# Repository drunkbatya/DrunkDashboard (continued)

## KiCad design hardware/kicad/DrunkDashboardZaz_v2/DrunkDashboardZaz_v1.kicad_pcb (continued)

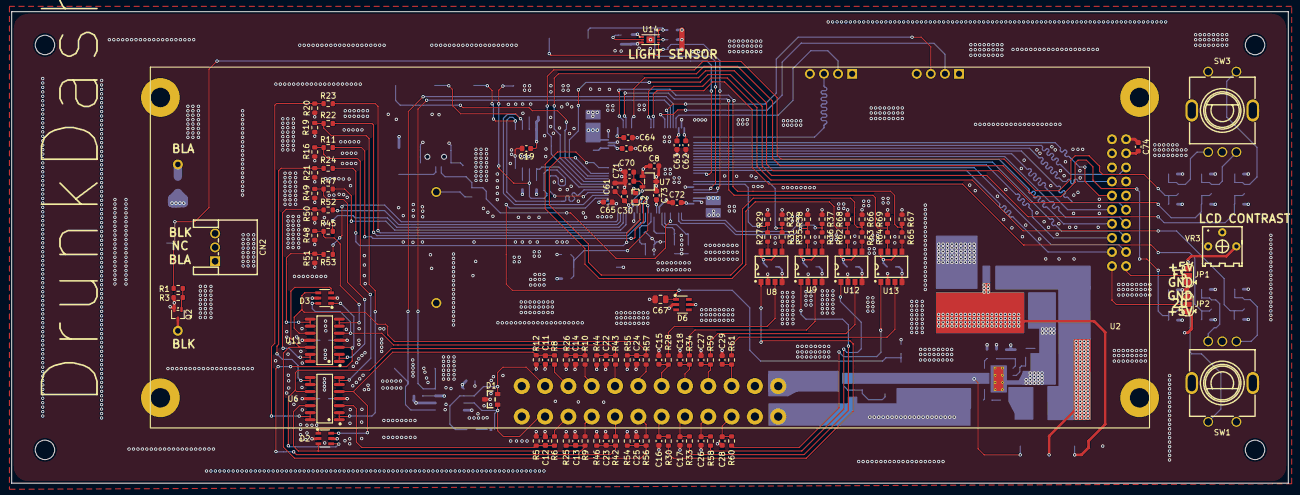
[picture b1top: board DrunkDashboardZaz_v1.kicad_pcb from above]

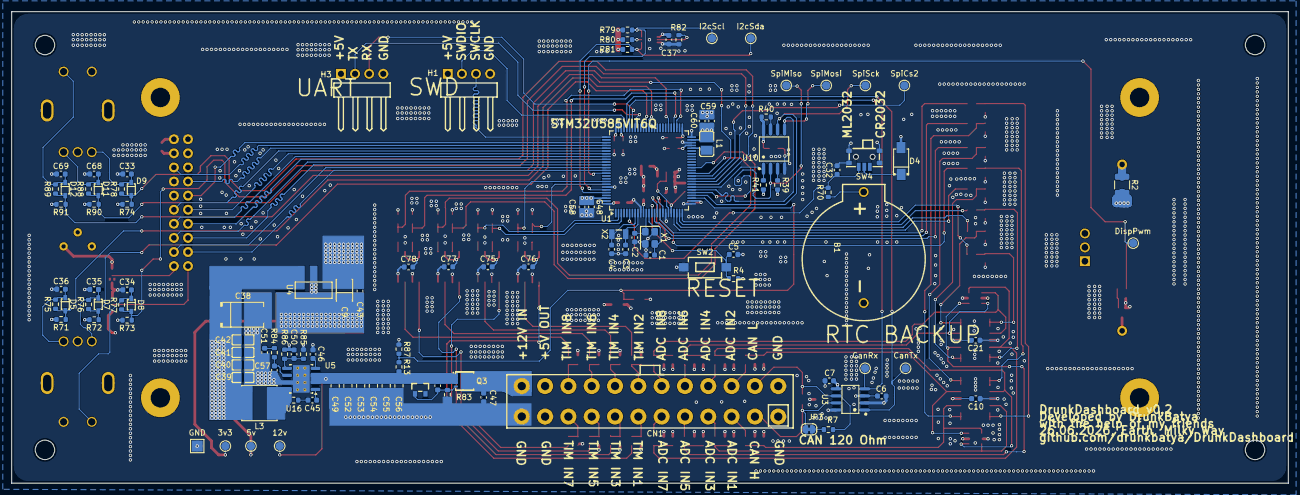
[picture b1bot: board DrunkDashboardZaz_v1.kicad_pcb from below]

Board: 4 copper layers, 230.0 x 84.9 mm, 223 parts (113 on the bottom side), 141 nets.

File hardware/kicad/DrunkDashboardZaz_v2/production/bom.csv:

Designator,Footprint,Quantity,Value,LCSC Part #
12V_1,TestPoint_Pad_D1.5mm,1,12v,
3V3_1,TestPoint_Pad_D1.5mm,1,3v3,
5V1,TestPoint_Pad_D1.5mm,1,5v,
B1,BS-02-A1AJ010,1,BS-02-A1AJ010,C5239862
"C1, C2, C3, C4",0603,4,CL10C180JB8NNNC,C1647
"C10, C11, C12, C13, C14, C15, C16, C17, C18, C19, C21, C22, C23, C24, C25, C26, C27, C28, C29, C30, C32, C37, C44, C45, C46, C48, C59, C6, C62, C63, C64, C65, C66, C7, C71, C72, C73, C74, C75, C76, C77, C78, C8",0603,43,CL10B104KB8NNNC,C1591
"C33, C34, C35, C36, C5, C68, C69",0603,7,CC0603KRX7R0BB103,C107059
C38,EEFCX0J101R,1,EEFCX0J101R,C189619
"C39, C40, C41, C42",GCM21BR71A106KE22L,4,GCM21BR71A106KE22L,C126586
C43,0603,1,CL10A475KO8NNNC,C19666
C47,0603,1,CC0603KRX7R0BB104,C113803
"C49, C52, C53, C54, C55, C56, C67",0805,7,GRM21BC8YA106KE11L,C469541
"C50, C57",0603,2,CC0603KRX7R0BB221,C107061
C51,0603,1,CC0603KRX7R9BB122,C107073
"C58, C60, C61",0603,3,GRM188R61H225KE11D,C162273
C70,0603,1,CC0603JRX7R7BB105,C519560
C9,25TQC22MYFB,1,25TQC22MYFB,C3018703
CANRX_1,TestPoint_Pad_D1.5mm,1,CanRx,
CANTX_1,TestPoint_Pad_D1.5mm,1,CanTx,
CN1,39281243,1,39281243,C114088
CN2,S3B-XH-A-1_LF_SN,1,S3B-XH-A-1_LF_SN,C163036
D1,PESD1CAN_215,1,PESD1CAN_215,C15771
D10,MMBZ5242BLT3G,1,MMBZ5242BLT3G,C896784
"D11, D12, D5, D7, D8, D9",1N4148WS_C917117,6,1N4148WS_C917117,C917117
"D2, D3, D6",SRV05-4_C558418,3,SRV05-4_C558418,C558418
D4,SS12_C18199177,1,SS12_C18199177,C18199177
DISPPWM1,TestPoint_Pad_D1.5mm,1,DispPwm,
GND1,TestPoint_Pad_2.0x2.0mm,1,GND,
"H1, H3",PZ254R-11-04P,2,PZ254R-11-04P,C492412
I2CSCL_1,TestPoint_Pad_D1.5mm,1,I2cScl,
I2CSDA_1,TestPoint_Pad_D1.5mm,1,I2cSda,
L1,LQM2HPN2R2MG0L,1,LQM2HPN2R2MG0L,C86092
L2,BLM18PG121SN1D_C14709,1,BLM18PG121SN1D_C14709,C14709
L3,SRN6045TA-3R3Y,1,SRN6045TA-3R3Y,C3221229
Q2,SOT-323_SC-70,1,2N7002WT1G,C232391
Q3,DMP3013SFV-7_ES,1,DMP3013SFV-7_ES,C42412325
"R1, R70",0603,2,PTFR0603B100RN9,C394538
"R10, R16, R19, R20, R21, R3, R39, R4, R40, R41, R42, R43, R48, R49, R50, R51, R56, R57, R6, R71, R72, R73, R74, R75, R76, R77, R78, R8, R87, R88, R89, R9, R90, R91",0603,34,RT0603BRD0710KL,C95204
"R11, R22, R23, R24, R45, R47, R52, R53",0603,8,FRC0603F5601TS,C2907046
R13,0603,1,FRC0603F8202TS,C2907072
R2,1210,1,RK73B2ETTD180J,C830159
"R27, R31, R35, R36, R62, R63, R64, R65",0603,8,FRC0603F2401TS,C2907007
"R28, R30, R33, R34, R58, R59, R60, R61",0603,8,FRC0603F6200TS,C2907058
"R29, R32, R37, R38, R66, R67, R68, R69, R79, R81, R82",0603,11,FRC0603F4701TS,C2907034
"R44, R46, R54, R55",0603,4,FRC0603F2701TS,C2907008
R7,0603,1,FRC0603F1200TS,C2906988
R80,0603,1,FRC0603F1001TS,C2907002
"R83, R86",0603,2,RC0603FR-0712KL,C114659
R84,0603,1,FRC0603F2002TS,C2907011
R85,0603,1,FRC0603F2201TS,C2907005
SPICS2_1,TestPoint_Pad_D1.5mm,1,SpiCs2,
SPIMISO_1,TestPoint_Pad_D1.5mm,1,SpiMiso,
SPIMOSI_1,TestPoint_Pad_D1.5mm,1,SpiMosi,
SPISCK_1,TestPoint_Pad_D1.5mm,1,SpiSck,
"SW1, SW3",EC11E15244G1,2,EC11E15244G1,C370970
SW2,TS3643TP,1,TS3643TP,C398054
SW4,MINI_MSK12CO2,1,MINI_MSK12CO2,C2681570
U1,LQFP-100_14x14mm_P0.5mm,1,STM32U585VIT6Q,C5270986
U10,W25Q32JVSSIQ_C179173,1,W25Q32JVSSIQ_C179173,C179173
"U11, U6",MCP6004T-I_SL,2,MCP6004T-I_SL,C7378
"U12, U13, U8, U9",ILD207T,4,ILD207T,C71049
U14,BH1750FVI-TR,1,BH1750FVI-TR,C78960
U16,0603,1,CRCW060310R0FKEAHP,C313648
U3,TJA1051T_3_1J,1,TJA1051T_3_1J,C38695
U4,AMS1117-3_3,1,AMS1117-3_3,C6186
U5,SOIC-8-1EP_3.9x4.9mm_P1.27mm_EP2.95x4.9mm_Mask2.71x3.4mm_ThermalVias,1,AP64501SP-13,C2071517
U7,REF3333AIDBZR,1,REF3333AIDBZR,C130016
VR3,3362P-1-103LF_C48997950,1,3362P-1-103LF_C48997950,C48997950
X1,Crystal_SMD_3225-4Pin_3.2x2.5mm,1,X322525MOB4SI,C9006
X2,Q13FC1350000400,1,Q13FC1350000400,C32346

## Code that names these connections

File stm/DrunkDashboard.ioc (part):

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Mcu.Name=STM32H743VITx
Mcu.Package=LQFP100
Mcu.UserName=STM32H743VITx
PA12.GPIOParameters=GPIO_Label
PA12.GPIO_Label=BACK_BTN
PA12.Signal=GPIO_Input
PA13\ (JTMS/SWDIO).Mode=Serial_Wire
PA13\ (JTMS/SWDIO).Signal=DEBUG_JTMS-SWDIO
PA14\ (JTCK/SWCLK).Mode=Serial_Wire
PA14\ (JTCK/SWCLK).Signal=DEBUG_JTCK-SWCLK
PA15\ (JTDI).GPIOParameters=GPIO_Label
PA15\ (JTDI).GPIO_Label=NOT_PROVIDED
PA15\ (JTDI).Signal=GPIO_Output
PA2.Mode=Asynchronous
PA2.Signal=USART2_TX
PA3.Mode=Asynchronous
PA3.Signal=USART2_RX
PA5.Mode=TX_Only_Simplex_Unidirect_Master
PA5.Signal=SPI1_SCK
PA6.GPIOParameters=GPIO_Speed,GPIO_Label
PA6.GPIO_Label=SPI1_DC
PA6.GPIO_Speed=GPIO_SPEED_FREQ_LOW
PA6.Signal=GPIO_Output
PA7.Mode=TX_Only_Simplex_Unidirect_Master
PA7.Signal=SPI1_MOSI
PB2.GPIOParameters=GPIO_PuPd,GPIO_Label
PB2.GPIO_Label=DISP4_CS
PB2.GPIO_PuPd=GPIO_PULLUP
PB2.Signal=GPIO_Output
PB4\ (NJTRST).GPIOParameters=GPIO_PuPd,GPIO_Label
PB4\ (NJTRST).GPIO_Label=DISP2_RES
PB4\ (NJTRST).GPIO_PuPd=GPIO_PULLUP
PB4\ (NJTRST).Signal=GPIO_Output
PB5.GPIOParameters=GPIO_PuPd,GPIO_Label
PB5.GPIO_Label=DISP3_RES
PB5.GPIO_PuPd=GPIO_PULLUP
PB5.Signal=GPIO_Output
PB6.GPIOParameters=GPIO_PuPd,GPIO_Label
PB6.GPIO_Label=DISP5_CS
PB6.GPIO_PuPd=GPIO_PULLUP
PB6.Signal=GPIO_Output
PB7.GPIOParameters=GPIO_PuPd,GPIO_Label
PB7.GPIO_Label=DISP3_CS
PB7.GPIO_PuPd=GPIO_PULLUP
PB7.Signal=GPIO_Output
PB8.GPIOParameters=GPIO_PuPd,GPIO_Label
PB8.GPIO_Label=DISP8_CS
PB8.GPIO_PuPd=GPIO_PULLUP
PB8.Signal=GPIO_Output
PB9.GPIOParameters=GPIO_PuPd,GPIO_Label
PB9.GPIO_Label=DISP5_RES
PB9.GPIO_PuPd=GPIO_PULLUP
PB9.Signal=GPIO_Output
PC10.GPIOParameters=GPIO_PuPd,GPIO_Label
PC10.GPIO_Label=DISP9_RES
PC10.GPIO_PuPd=GPIO_PULLUP
PC10.Signal=GPIO_Output
PC11.GPIOParameters=GPIO_PuPd,GPIO_Label
PC11.GPIO_Label=ENC_BTN
PC11.GPIO_PuPd=GPIO_PULLUP
PC11.Signal=GPIO_Input
PC12.GPIOParameters=GPIO_PuPd,GPIO_Label
PC12.GPIO_Label=DISP6_RES
PC12.GPIO_PuPd=GPIO_PULLUP
PC12.Signal=GPIO_Output
PD1.GPIOParameters=GPIO_PuPd,GPIO_Label
PD1.GPIO_Label=DISP9_CS
PD1.GPIO_PuPd=GPIO_PULLUP
PD1.Signal=GPIO_Output
PD4.GPIOParameters=GPIO_PuPd,GPIO_Label
PD4.GPIO_Label=DISP6_CS
PD4.GPIO_PuPd=GPIO_PULLUP
PD4.Signal=GPIO_Output
PD7.GPIOParameters=GPIO_PuPd,GPIO_Label
PD7.GPIO_Label=DISP2_CS
PD7.GPIO_PuPd=GPIO_PULLUP
PD7.Signal=GPIO_Output
PE1.GPIOParameters=GPIO_PuPd,GPIO_Label
PE1.GPIO_Label=DISP8_RES
PE1.GPIO_PuPd=GPIO_PULLUP
PE1.Signal=GPIO_Output
PE10.GPIOParameters=GPIO_PuPd,GPIO_Label
PE10.GPIO_Label=DISP7_RES
PE10.GPIO_PuPd=GPIO_PULLUP
PE10.Signal=GPIO_Output
PE11.Signal=S_TIM1_CH2
PE12.GPIOParameters=GPIO_PuPd,GPIO_Label
PE12.GPIO_Label=DISP1_RES
PE12.GPIO_PuPd=GPIO_PULLUP
PE12.Signal=GPIO_Output
PE13.GPIOParameters=GPIO_PuPd,GPIO_Label
PE13.GPIO_Label=DISP1_CS
PE13.GPIO_PuPd=GPIO_PULLUP
PE13.Signal=GPIO_Output
PE7.GPIOParameters=GPIO_PuPd,GPIO_Label
PE7.GPIO_Label=DISP4_RES
PE7.GPIO_PuPd=GPIO_PULLUP
PE7.Signal=GPIO_Output
PE8.GPIOParameters=GPIO_PuPd,GPIO_Label
PE8.GPIO_Label=DISP7_CS
PE8.GPIO_PuPd=GPIO_PULLUP
PE8.Signal=GPIO_Output
PE9.Signal=S_TIM1_CH1
PH0-OSC_IN\ (PH0).Mode=HSE-External-Oscillator
PH0-OSC_IN\ (PH0).Signal=RCC_OSC_IN
PH1-OSC_OUT\ (PH1).Mode=HSE-External-Oscillator
PH1-OSC_OUT\ (PH1).Signal=RCC_OSC_OUT
RCC.SYSCLKFreq_VALUE=400000000
RCC.SYSCLKSource=RCC_SYSCLKSOURCE_PLLCLK
board=custom

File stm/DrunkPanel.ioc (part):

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Mcu.Name=STM32F411C(C-E)Ux
Mcu.Package=UFQFPN48
Mcu.UserName=STM32F411CEUx
PA4.GPIOParameters=GPIO_Label
PA4.GPIO_Label=SPI1_RST
PA4.Signal=GPIO_Output
PA5.Mode=TX_Only_Simplex_Unidirect_Master
PA5.Signal=SPI1_SCK
PA6.GPIOParameters=GPIO_Label
PA6.GPIO_Label=SPI1_CE
PA6.Signal=GPIO_Output
PA7.Mode=TX_Only_Simplex_Unidirect_Master
PA7.Signal=SPI1_MOSI
PB0.GPIOParameters=GPIO_Label
PB0.GPIO_Label=SPI1_DC
PB0.Signal=GPIO_Output
PB10.Mode=TX_Only_Simplex_Unidirect_Master
PB10.Signal=SPI2_SCK
PB13.GPIOParameters=GPIO_Label
PB13.GPIO_Label=SPI2_DC
PB13.Signal=GPIO_Output
PB14.GPIOParameters=GPIO_Label
PB14.GPIO_Label=SPI2_CE
PB14.Signal=GPIO_Output
PB15.Mode=TX_Only_Simplex_Unidirect_Master
PB15.Signal=SPI2_MOSI
PH0\ -\ OSC_IN.Mode=HSE-External-Oscillator
PH0\ -\ OSC_IN.Signal=RCC_OSC_IN
PH1\ -\ OSC_OUT.Mode=HSE-External-Oscillator
PH1\ -\ OSC_OUT.Signal=RCC_OSC_OUT
RCC.HSE_VALUE=25000000
RCC.SYSCLKFreq_VALUE=100000000
RCC.SYSCLKSource=RCC_SYSCLKSOURCE_PLLCLK
board=custom

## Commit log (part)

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2023-09-12 Init commit
2023-09-12 Remove extra code
2023-09-12 Working single display
2023-09-12 Add working two displays
2023-09-12 Migrating to STM32H7
2023-09-13 Add setiing FIFO threshold
2023-09-13 Trying to use SPI init from example
2023-09-14 SPI works!!
2023-09-14 Format code, add glue
2023-09-15 Starting porting canvas
2023-09-16 Add icons
2023-09-16 Add first icon
2023-09-17 Add mlib submodule, first scene
2023-09-19 Add separate private headers
2023-09-19 Restructure
2023-09-19 Add Gui
2023-09-19 Add malloc wrap
2023-09-19 Start using scene_manager
2023-09-20 Add FreeRTOS from ST
2023-09-21 Changing memmory allocation type
2023-09-22 Add separate memmory allocator file
2023-09-22 Add auto heap in ld script
2023-09-24 Temp migrate to H750
2023-09-29 Restructure all
2023-09-30 Add separate GUI thread
